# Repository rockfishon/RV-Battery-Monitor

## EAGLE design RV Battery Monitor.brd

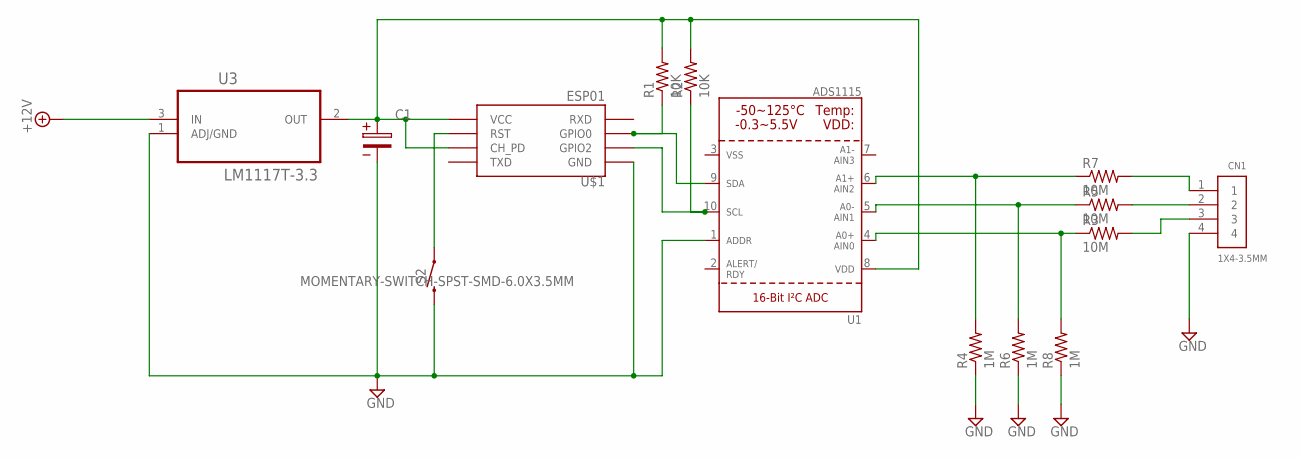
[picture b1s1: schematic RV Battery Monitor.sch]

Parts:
C1: WCAP-AT1H_10X16_860241375002; 10X5X0.9(DXAXB)
CN1: 1X4-3.5MM; 1X04-3.5MM
R1, R2: 10K; 0207/7
R3, R5, R7: 10M; 0207/7
R4, R6, R8: 1M; 0207/7
S2: MOMENTARY-SWITCH-SPST-SMD-6.0X3.5MM; TACTILE_SWITCH_SMD_6.0X3.5MM
U1: ADS1115; MSOP10
U3: LM1117T-3.3; TO254P470X1016X2222-3P
U$1: ESP01

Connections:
+12V: U3.3 (IN)
GND: C1.2, CN1.4, R4.1, R6.1, R8.1, S2.2, U1.1 (ADDR), U3.1 (ADJ/GND), U$1.GND
unnamed: R2.1, U1.10 (SCL), U$1.GPIO2
unnamed: R1.1, U1.9 (SDA), U$1.GPIO0
unnamed: R3.1, R8.2, U1.4 (AIN0)
unnamed: R5.1, R6.2, U1.5 (AIN1)
unnamed: R4.2, R7.1, U1.6 (AIN2)
unnamed: CN1.1, R7.2
unnamed: CN1.2, R5.2
unnamed: CN1.3, R3.2
unnamed: S2.1, U$1.RST
unnamed: C1.1, R1.2, R2.2, U1.8 (VDD), U3.2 (OUT), U$1.CH_PD, U$1.VCC

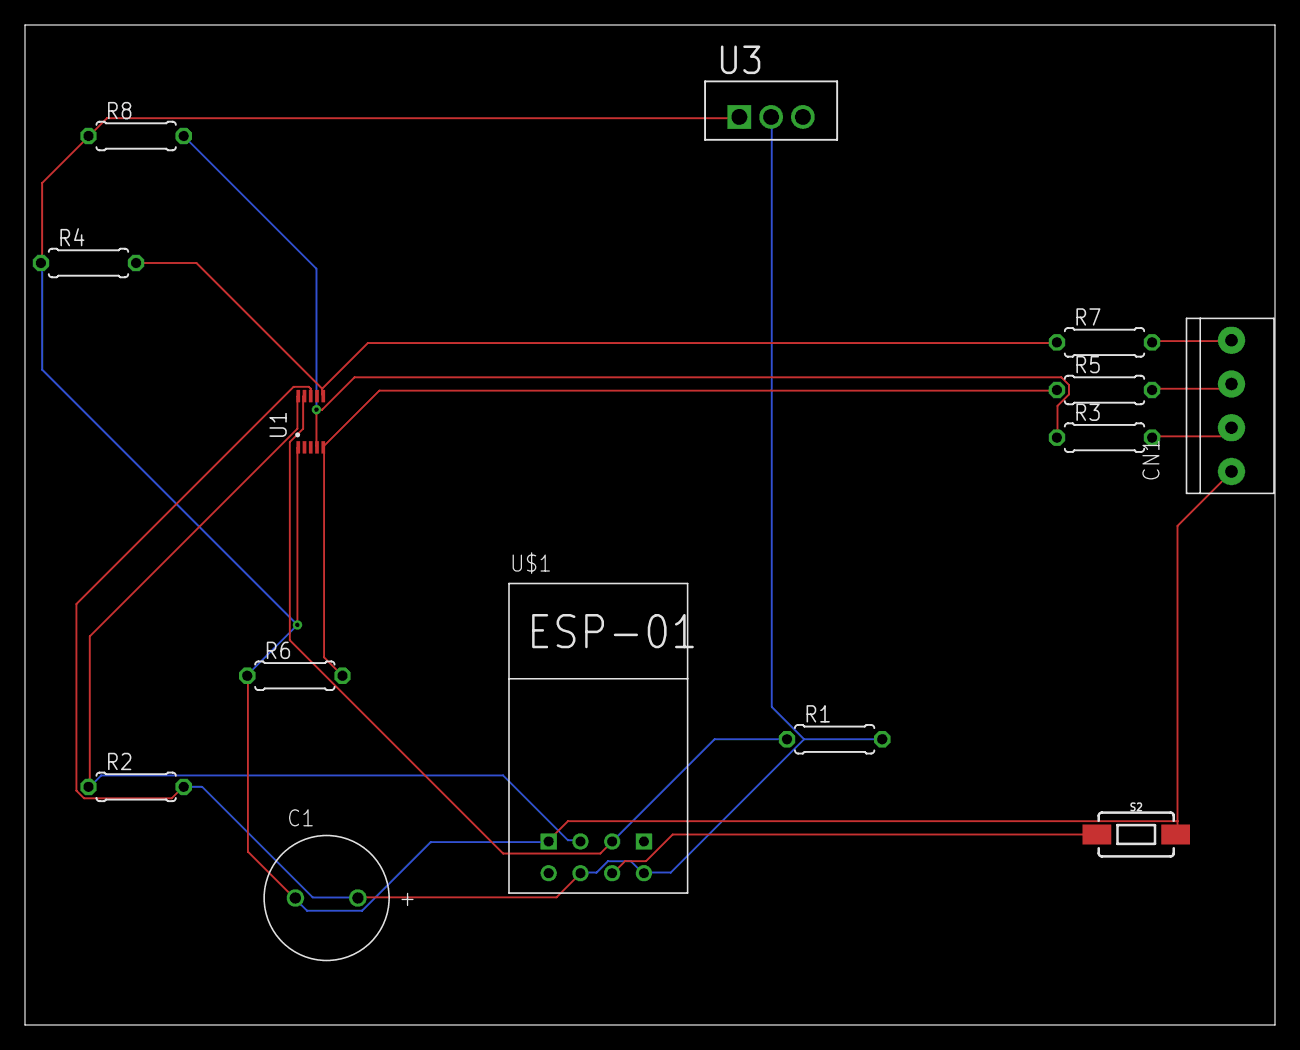
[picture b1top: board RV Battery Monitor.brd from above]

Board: 2 copper layers, 100.0 x 80.0 mm, 14 parts (0 on the bottom side), 11 nets.

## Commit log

2020-01-16 Create LICENSE

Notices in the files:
parts and their libraries:
Wurth_Elektronik_Passive_Capacitors_rev1: Copyright: Würth Elektronik
SparkFun-Switches: Licensing: Creative Commons ShareAlike 4.0 International - https://creativecommons.org/licenses/by-sa/4.0
